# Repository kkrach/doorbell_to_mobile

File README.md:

# doorbell_to_mobile
Forward door bell to mobile phone

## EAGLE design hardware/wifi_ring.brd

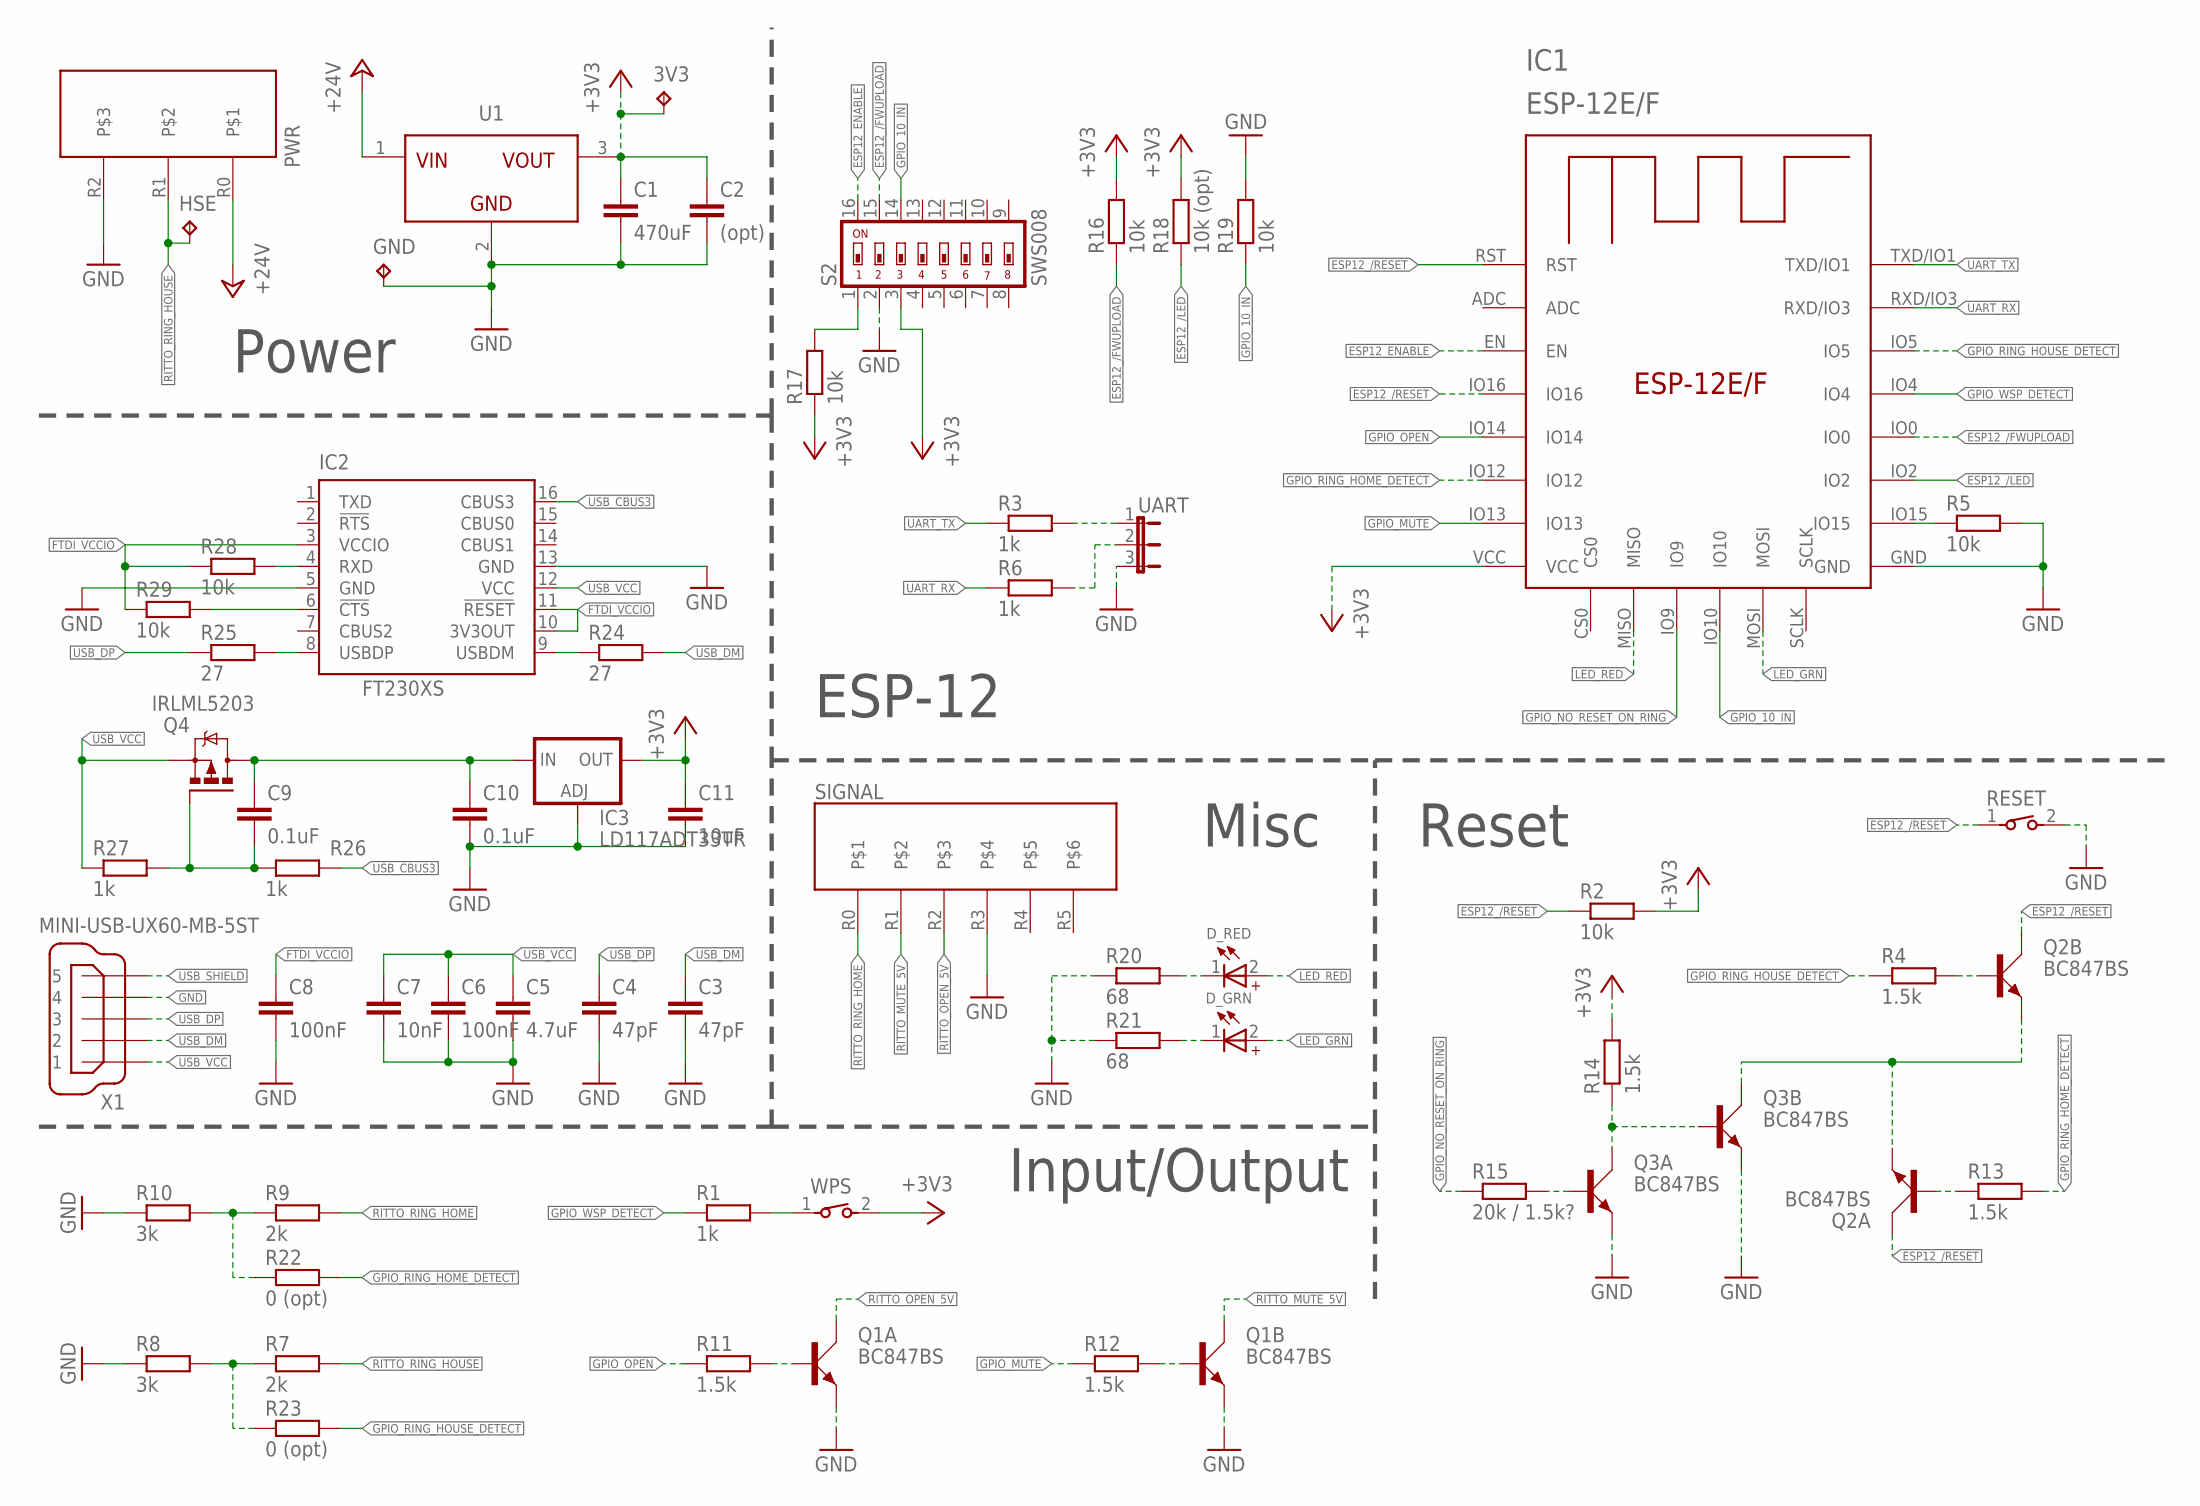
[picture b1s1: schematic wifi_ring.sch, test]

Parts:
3V3: TPTP10SQ; TP10SQ
C1: 470uF; C1206
C2: (opt); C1206
C3, C4: 47pF; C1206
C5: 4.7uF; C1206
C6, C8: 100nF; C1206
C7: 10nF; C1206
C9, C10: 0.1uF; C1206
C11: 10uF; C1206
D_GRN: WL-SMRW_1206_CYL_156120VS75300_NOR; WL-SMRW_1206_CYL
D_RED: WL-SMRW_1206_CYL_156120RS75300_NOR; WL-SMRW_1206_CYL
GND: TPTP10SQ; TP10SQ
HSE: TPTP10SQ; TP10SQ
IC1: ESP-12E/F; ESP-12E
IC2: FT230XS; SSOP16
IC3: LD117ADT33TR; DPACK
PWR: RAST_3
Q1, Q2, Q3: BC847BS; SOT363_PHILIPS
Q4: IRLML5203; MICRO3
R1, R3, R6, R26, R27: 1k; R1206
R2, R5, R16, R17, R19, R28, R29: 10k; R1206
R4, R11, R12, R13, R14: 1.5k; R1206
R7, R9: 2k; R1206
R8, R10: 3k; R1206
R15: 20k / 1.5k?; R1206
R18: 10k (opt); R1206
R20, R21: 68; R1206
R22, R23: 0 (opt); R1206
R24, R25: 27; R1206
RESET: 434123025816
S2: SWS008; SMS-008
SIGNAL: RAST_6
U1: MAGI³C-FDSM_SIP-3_173950378_17395XX78; MAGI³C-FDSM_17395XX78
UART: JP2E; JP2
WPS: 434123025816
X1: MINI-USB-UX60-MB-5ST; UX60-MB-5ST

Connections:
+3V3: 3V3.TP, C1.1, C2.1, C11.1, IC1.VCC, IC3.4 (OUT), R2.2, R14.2, R16.2, R17.1, R18.2, S2.3, U1.3 (VOUT), WPS.2
+24V: PWR.R0, U1.1 (VIN)
ESP12_/FWUPLOAD: IC1.IO0, R16.1, S2.15
ESP12_/LED: IC1.IO2, R18.1
ESP12_/RESET: IC1.IO16, IC1.RST, Q2.3 (C), Q2.6 (C), R2.1, RESET.1
ESP12_ENABLE: IC1.EN, S2.16
FTDI_VCCIO: C8.1, IC2.3 (VCCIO), IC2.10 (3V3OUT), IC2.11 (!RESET), R28.1, R29.1
GND: C1.2, C2.2, C3.2, C4.2, C5.2, C6.2, C7.2, C8.2, C10.2, C11.2, GND.TP, IC1.GND, IC2.5 (GND), IC2.13 (GND), IC3.1 (ADJ), PWR.R2, Q1.1 (E), Q1.4 (E), Q3.1 (E), Q3.4 (E), R5.2, R8.1, R10.1, R19.2, R20.1, R21.1, RESET.2, S2.2, SIGNAL.R3, U1.2 (GND), UART.3, X1.4
GPIO_10_IN: IC1.IO10, R19.1, S2.14
GPIO_MUTE: IC1.IO13, R12.1
GPIO_NO_RESET_ON_RING: IC1.IO9, R15.1
GPIO_OPEN: IC1.IO14, R11.1
GPIO_RING_HOME_DETECT: IC1.IO12, R13.2, R22.2
GPIO_RING_HOUSE_DETECT: IC1.IO5, R4.1, R23.2
GPIO_WSP_DETECT: IC1.IO4, R1.1
LED_GRN: D_GRN.2 (+), IC1.MOSI
LED_RED: D_RED.2 (+), IC1.MISO
unnamed: R3.2, UART.1
unnamed: R6.2, UART.2
unnamed: IC1.IO15, R5.1
unnamed: R1.2, WPS.1
unnamed: R7.1, R8.2, R23.1
unnamed: R9.1, R10.2, R22.1
unnamed: R17.2, S2.1
unnamed: Q2.5 (B), R4.2
unnamed: Q2.2 (B), R13.1
unnamed: Q1.2 (B), R11.2
unnamed: Q1.5 (B), R12.2
unnamed: D_RED.1 (-), R20.2
unnamed: D_GRN.1 (-), R21.2
unnamed: Q3.5 (B), Q3.6 (C), R14.1
unnamed: Q3.2 (B), R15.2
unnamed: Q2.1 (E), Q2.4 (E), Q3.3 (C)
unnamed: IC2.9 (USBDM), R24.1
unnamed: C9.2, Q4.1 (G), R26.1, R27.2
unnamed: IC2.8 (USBDP), R25.2
unnamed: C9.1, C10.1, IC3.3 (IN), Q4.3 (D)
unnamed: IC2.4 (RXD), R28.2
unnamed: IC2.6 (!CTS), R29.2
RITTO_MUTE_5V: Q1.3 (C), SIGNAL.R1
RITTO_OPEN_5V: Q1.6 (C), SIGNAL.R2
RITTO_RING_HOME: R9.2, SIGNAL.R0
RITTO_RING_HOUSE: HSE.TP, PWR.R1, R7.2
UART_RX: IC1.RXD/IO3, R6.1
UART_TX: IC1.TXD/IO1, R3.1
USB_CBUS3: IC2.16 (CBUS3), R26.2
USB_DM: C3.1, R24.2, X1.2
USB_DP: C4.1, R25.1, X1.3
USB_SHIELD: X1.5
USB_VCC: C5.1, C6.1, C7.1, IC2.12 (VCC), Q4.2 (S), R27.1, X1.1

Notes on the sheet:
Power
Reset
ESP-12
Input/Output
Misc

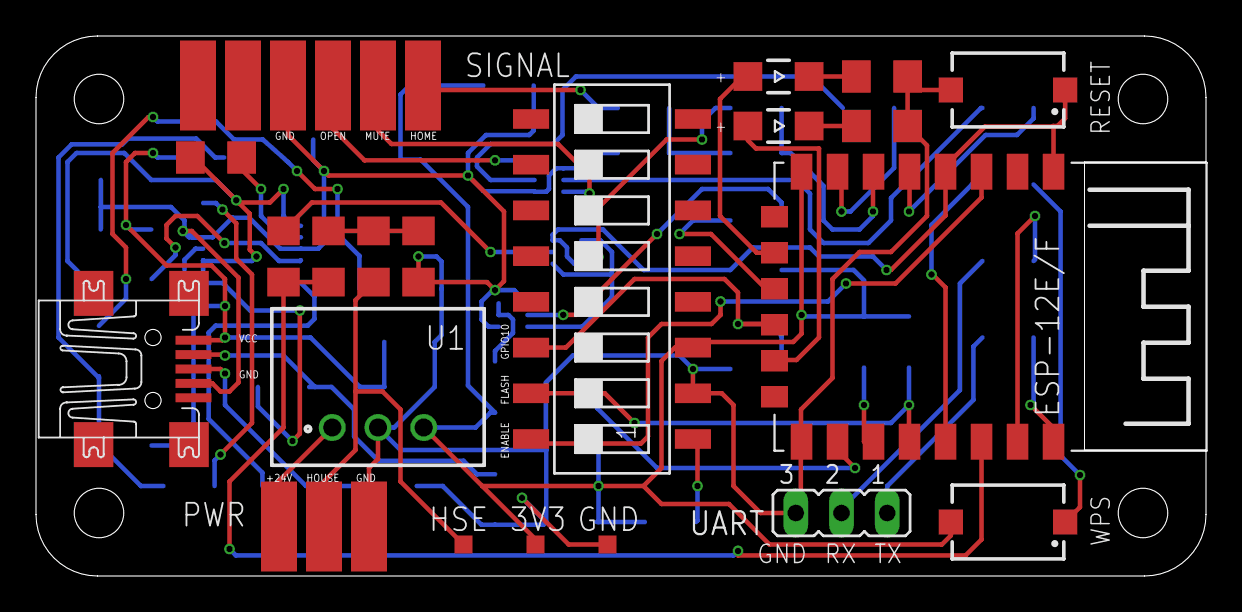
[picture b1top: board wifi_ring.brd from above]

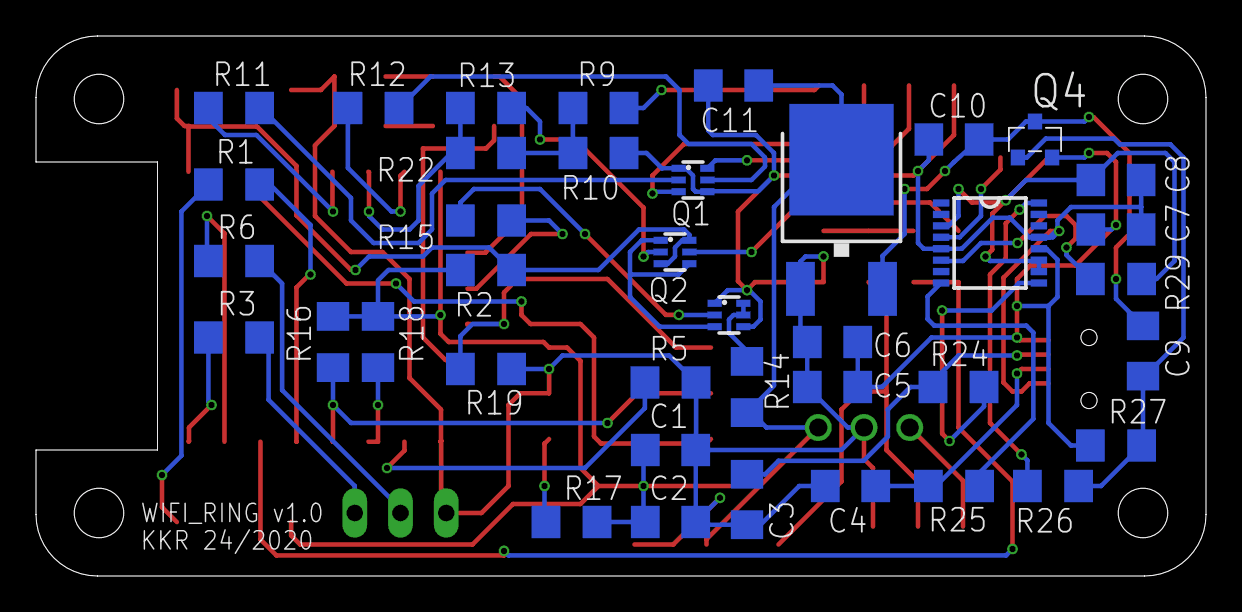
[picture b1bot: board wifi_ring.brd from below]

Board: 2 copper layers, 65.0 x 30.0 mm, 60 parts (39 on the bottom side), 49 nets.

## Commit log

2020-05-24 Initial checkin of hw (EAGLE files)
2020-05-24 Adding hardware documentation
2020-05-24 Adding latest version of schematic
2020-05-24 Replacing Vcc with V3.3
2020-05-24 Checkpoint commit for board file
2020-05-24 Adding RAST library
2020-05-25 Placing elements in layout
2020-05-26 Layout resolved
2020-05-27 Checkpoint commit
2020-06-01 Adding USB/FTDI
2020-06-02 Checkpoint commit layout
2020-06-04 Finalizing board file
2020-06-04 Adding Eagle libraries
2020-06-04 Renaming and adding PDFs
2020-06-04 Adding latest layout changes for eurocircuits order
2020-06-25 Adding prototype project
2020-12-17 Adding setup.sh for downloading/setup environment/libraries
2020-12-17 Upgrade RTOS SDK to v3.3
2020-12-19 Correcting static server IP address
2020-12-19 Renaming sdkconfig
2020-12-19 Adding script description
2020-12-19 Initial check-in of firmware
    based on native ota-update example

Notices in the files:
parts and their libraries:
434123025816_Eagle_WS-TASV_rev20a: Copyright: Würth Elektronik
